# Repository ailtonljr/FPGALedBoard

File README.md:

# FPGALedBoard
Um módulo para a placa DE0-Nano com saídas em Leds e Display de 7 Segmentos.

Associação dos pinos da placa de saída com o FPGA:

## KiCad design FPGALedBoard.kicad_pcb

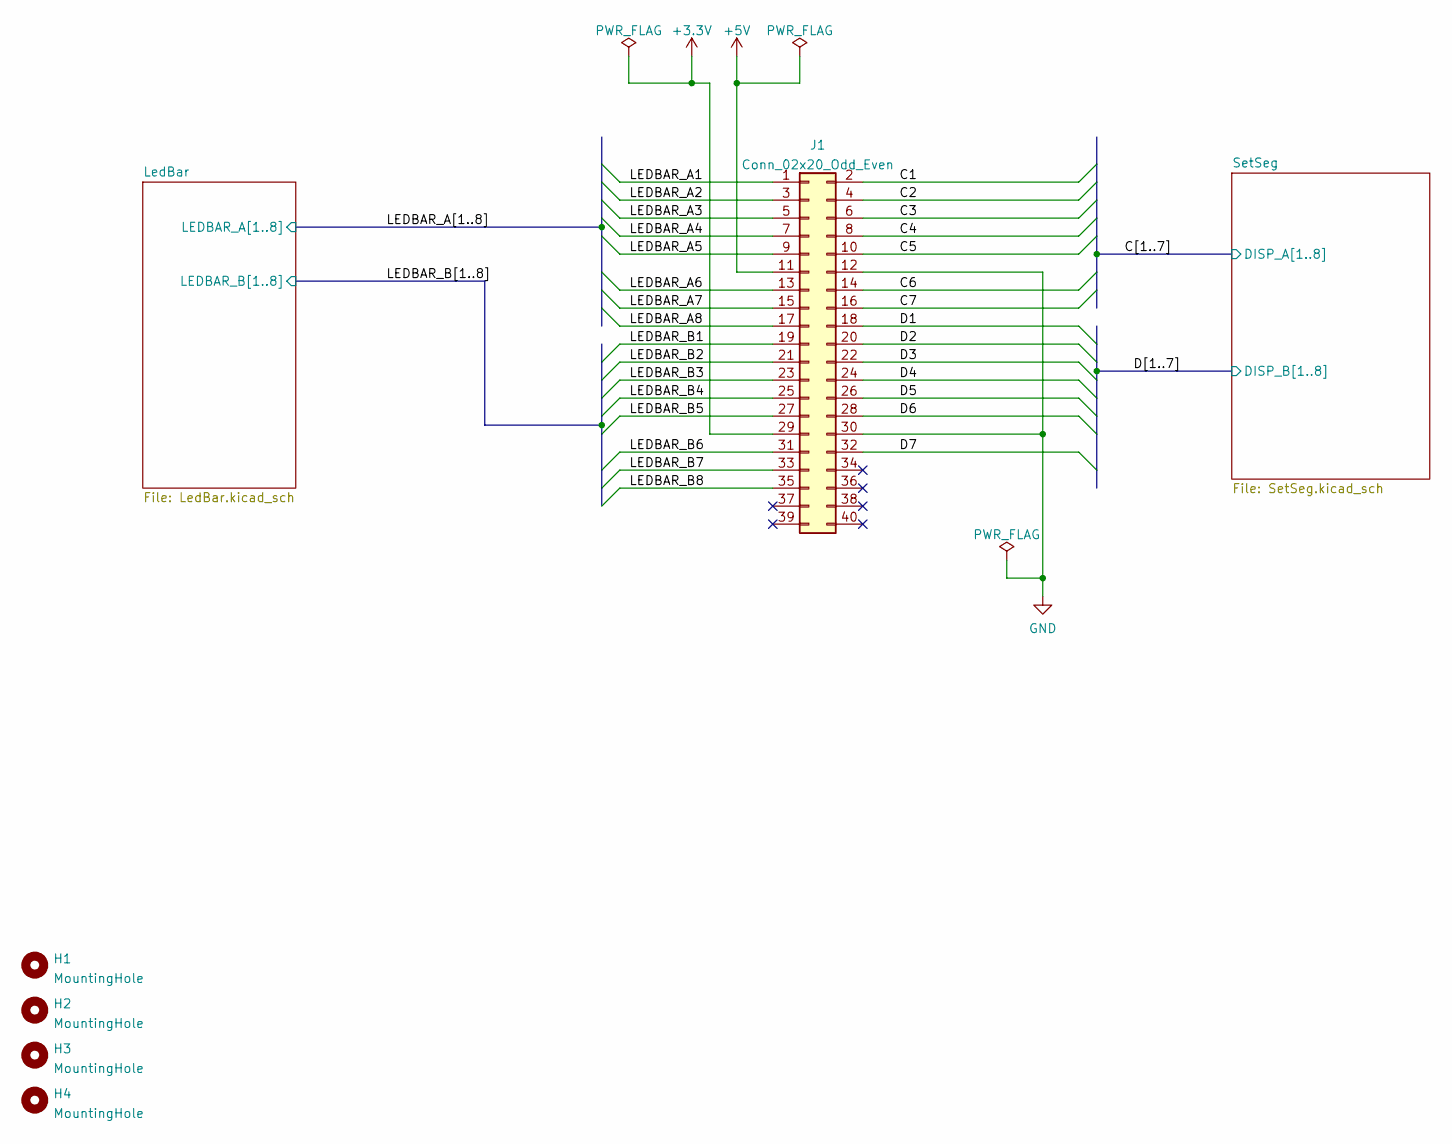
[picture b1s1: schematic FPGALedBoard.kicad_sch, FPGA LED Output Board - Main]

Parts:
H1, H2, H3, H4: MountingHole; MountingHole_3.2mm_M3
J1: Conn_02x20_Odd_Even; PinSocket_2x20_P2.54mm_Vertical

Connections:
+3V3: J1.29
+5V: J1.11; also elsewhere on the board
/C1: J1.2; also elsewhere on the board
/C2: J1.4; also elsewhere on the board
/C3: J1.6; also elsewhere on the board
/C4: J1.8; also elsewhere on the board
/C5: J1.10; also elsewhere on the board
/C6: J1.14; also elsewhere on the board
/C7: J1.16; also elsewhere on the board
/D1: J1.18; also elsewhere on the board
/D2: J1.20; also elsewhere on the board
/D3: J1.22; also elsewhere on the board
/D4: J1.24; also elsewhere on the board
/D5: J1.26; also elsewhere on the board
/D6: J1.28; also elsewhere on the board
/D7: J1.32; also elsewhere on the board
/LEDBAR_A1: J1.1; also elsewhere on the board
/LEDBAR_A2: J1.3; also elsewhere on the board
/LEDBAR_A3: J1.5; also elsewhere on the board
/LEDBAR_A4: J1.7; also elsewhere on the board
/LEDBAR_A5: J1.9; also elsewhere on the board
/LEDBAR_A6: J1.13; also elsewhere on the board
/LEDBAR_A7: J1.15; also elsewhere on the board
/LEDBAR_A8: J1.17; also elsewhere on the board
/LEDBAR_B1: J1.19; also elsewhere on the board
/LEDBAR_B2: J1.21; also elsewhere on the board
/LEDBAR_B3: J1.23; also elsewhere on the board
/LEDBAR_B4: J1.25; also elsewhere on the board
/LEDBAR_B5: J1.27; also elsewhere on the board
/LEDBAR_B6: J1.31; also elsewhere on the board
/LEDBAR_B7: J1.33; also elsewhere on the board
/LEDBAR_B8: J1.35; also elsewhere on the board
GND: J1.12, J1.30; also elsewhere on the board

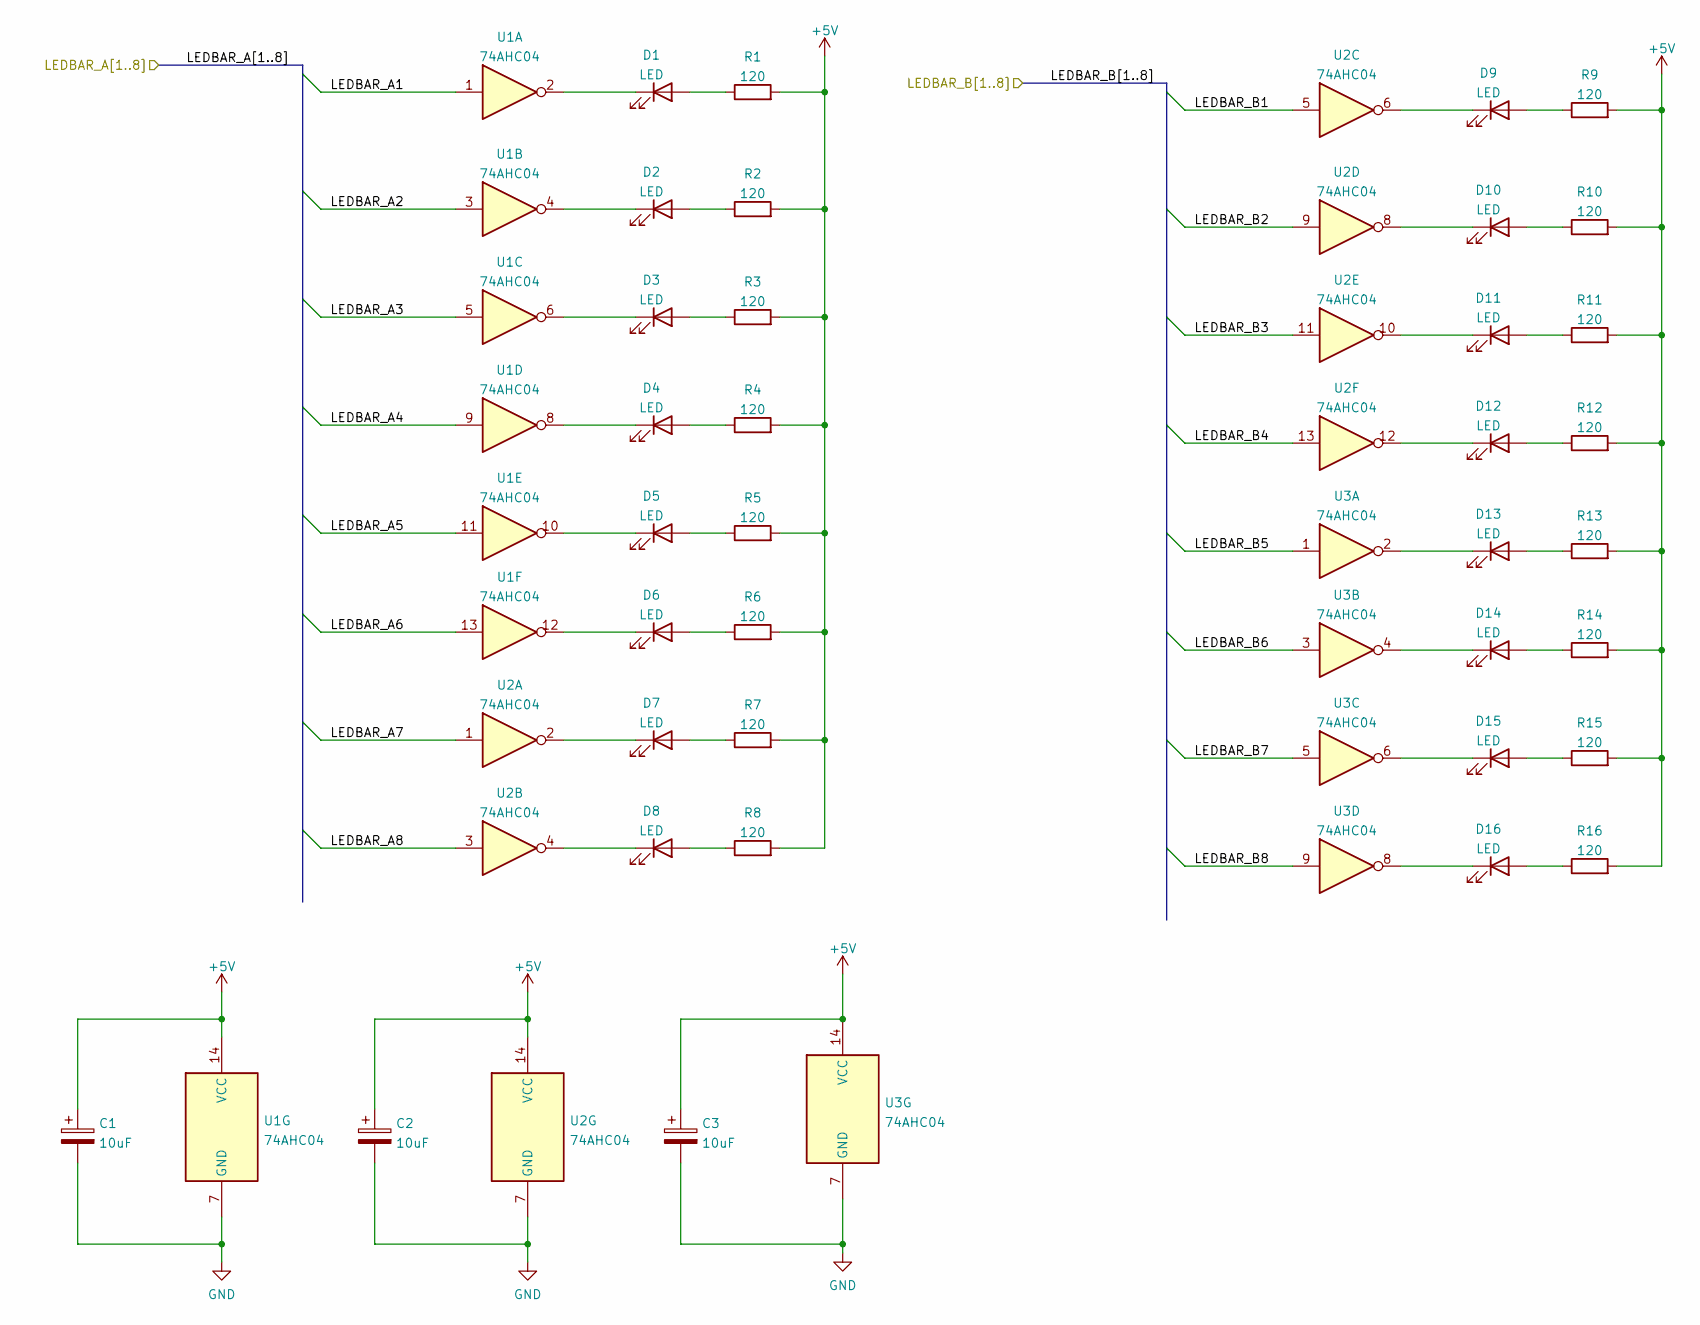
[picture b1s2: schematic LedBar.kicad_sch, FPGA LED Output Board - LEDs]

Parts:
C1, C2, C3: 10uF; CP_Radial_D5.0mm_P2.50mm
D1, D2, D3, D4, D5, D6, D7, D8, D9, D10, D11, D12, D13, D14, D15, D16: LED; LED_D3.0mm
R1, R2, R3, R4, R5, R6, R7, R8, R9, R10, R11, R12, R13, R14, R15, R16: 120; R_Axial_DIN0207_L6.3mm_D2.5mm_P7.62mm_Horizontal
U1, U2, U3: 74AHC04; DIP-14_W7.62mm

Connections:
+5V: C1.1, C2.1, C3.1, R1.2, R2.2, R3.2, R4.2, R5.2, R6.2, R7.2, R8.2, R9.2, R10.2, R11.2, R12.2, R13.2, R14.2, R15.2, R16.2, U1.14 (VCC), U2.14 (VCC), U3.14 (VCC); also elsewhere on the board
/LEDBAR_A1: U1.1; also elsewhere on the board
/LEDBAR_A2: U1.3; also elsewhere on the board
/LEDBAR_A3: U1.5; also elsewhere on the board
/LEDBAR_A4: U1.9; also elsewhere on the board
/LEDBAR_A5: U1.11; also elsewhere on the board
/LEDBAR_A6: U1.13; also elsewhere on the board
/LEDBAR_A7: U2.1; also elsewhere on the board
/LEDBAR_A8: U2.3; also elsewhere on the board
/LEDBAR_B1: U2.5; also elsewhere on the board
/LEDBAR_B2: U2.9; also elsewhere on the board
/LEDBAR_B3: U2.11; also elsewhere on the board
/LEDBAR_B4: U2.13; also elsewhere on the board
/LEDBAR_B5: U3.1; also elsewhere on the board
/LEDBAR_B6: U3.3; also elsewhere on the board
/LEDBAR_B7: U3.5; also elsewhere on the board
/LEDBAR_B8: U3.9; also elsewhere on the board
GND: C1.2, C2.2, C3.2, U1.7 (GND), U2.7 (GND), U3.7 (GND); also elsewhere on the board
unnamed: D1.1 (K), U1.2
unnamed: D1.2 (A), R1.1
unnamed: D2.1 (K), U1.4
unnamed: D2.2 (A), R2.1
unnamed: D3.1 (K), U1.6
unnamed: D3.2 (A), R3.1
unnamed: D4.1 (K), U1.8
unnamed: D4.2 (A), R4.1
unnamed: D5.1 (K), U1.10
unnamed: D5.2 (A), R5.1
unnamed: D6.1 (K), U1.12
unnamed: D6.2 (A), R6.1
unnamed: D7.1 (K), U2.2
unnamed: D7.2 (A), R7.1
unnamed: D8.1 (K), U2.4
unnamed: D8.2 (A), R8.1
unnamed: D9.1 (K), U2.6
unnamed: D9.2 (A), R9.1
unnamed: D10.1 (K), U2.8
unnamed: D10.2 (A), R10.1
unnamed: D11.1 (K), U2.10
unnamed: D11.2 (A), R11.1
unnamed: D12.1 (K), U2.12
unnamed: D12.2 (A), R12.1
unnamed: D13.1 (K), U3.2
unnamed: D13.2 (A), R13.1
unnamed: D14.1 (K), U3.4
unnamed: D14.2 (A), R14.1
unnamed: D15.1 (K), U3.6
unnamed: D15.2 (A), R15.1
unnamed: D16.1 (K), U3.8
unnamed: D16.2 (A), R16.1

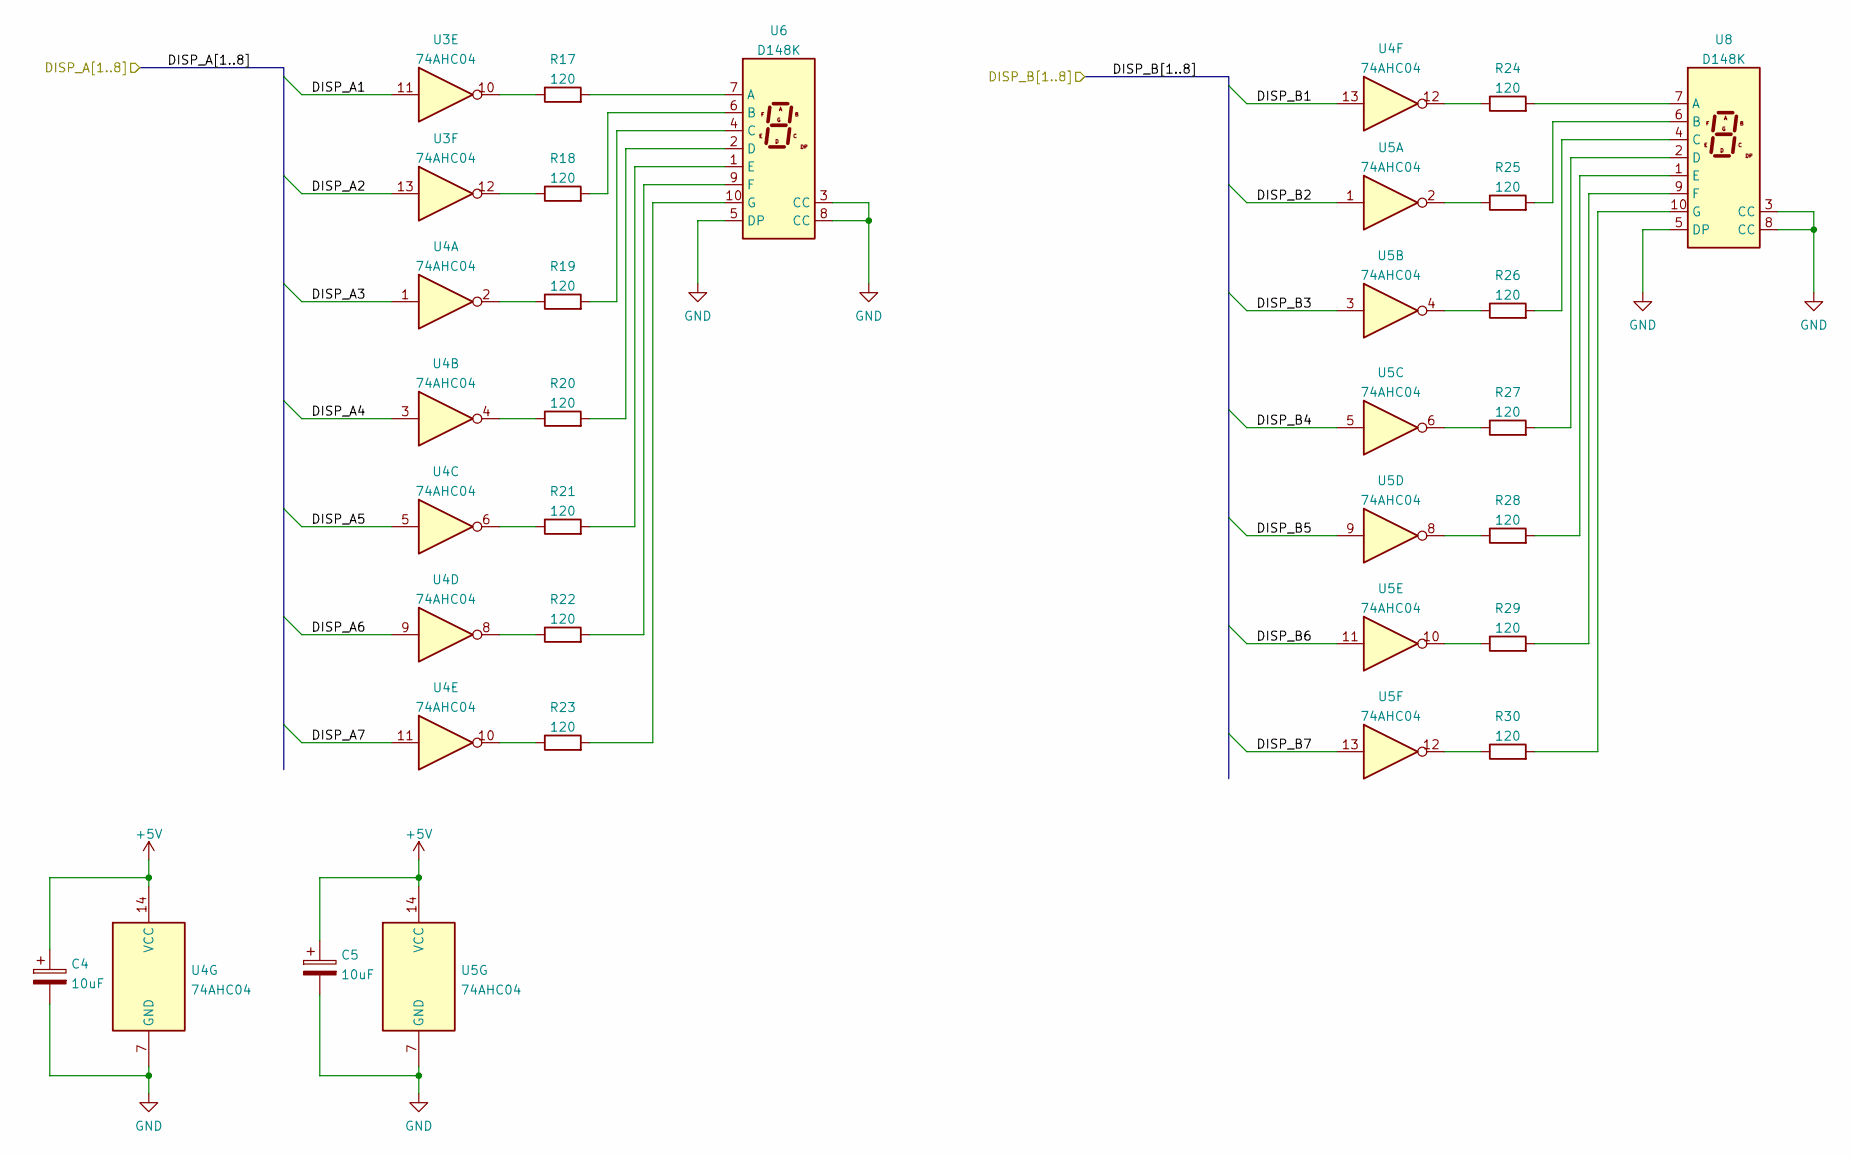
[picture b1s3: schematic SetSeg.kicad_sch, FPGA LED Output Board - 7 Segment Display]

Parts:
C4, C5: 10uF; CP_Radial_D5.0mm_P2.50mm
R17, R18, R19, R20, R21, R22, R23, R24, R25, R26, R27, R28, R29, R30: 120; R_Axial_DIN0207_L6.3mm_D2.5mm_P7.62mm_Horizontal
U3, U4, U5: 74AHC04; DIP-14_W7.62mm
U6, U8: D148K; D1X8K

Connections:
+5V: C4.1, C5.1, U4.14 (VCC), U5.14 (VCC); also elsewhere on the board
/C1: U3.11; also elsewhere on the board
/C2: U3.13; also elsewhere on the board
/C3: U4.1; also elsewhere on the board
/C4: U4.3; also elsewhere on the board
/C5: U4.5; also elsewhere on the board
/C6: U4.9; also elsewhere on the board
/C7: U4.11; also elsewhere on the board
/D1: U4.13; also elsewhere on the board
/D2: U5.1; also elsewhere on the board
/D3: U5.3; also elsewhere on the board
/D4: U5.5; also elsewhere on the board
/D5: U5.9; also elsewhere on the board
/D6: U5.11; also elsewhere on the board
/D7: U5.13; also elsewhere on the board
GND: C4.2, C5.2, U4.7 (GND), U5.7 (GND), U6.3 (CC), U6.5 (DP), U6.8 (CC), U8.3 (CC), U8.5 (DP), U8.8 (CC); also elsewhere on the board
unnamed: R17.1, U3.10
unnamed: R17.2, U6.7 (A)
unnamed: R18.1, U3.12
unnamed: R18.2, U6.6 (B)
unnamed: R19.1, U4.2
unnamed: R19.2, U6.4 (C)
unnamed: R20.1, U4.4
unnamed: R20.2, U6.2 (D)
unnamed: R21.1, U4.6
unnamed: R21.2, U6.1 (E)
unnamed: R22.1, U4.8
unnamed: R22.2, U6.9 (F)
unnamed: R23.1, U4.10
unnamed: R23.2, U6.10 (G)
unnamed: R24.1, U4.12
unnamed: R24.2, U8.7 (A)
unnamed: R25.1, U5.2
unnamed: R25.2, U8.6 (B)
unnamed: R26.1, U5.4
unnamed: R26.2, U8.4 (C)
unnamed: R27.1, U5.6
unnamed: R27.2, U8.2 (D)
unnamed: R28.1, U5.8
unnamed: R28.2, U8.1 (E)
unnamed: R29.1, U5.10
unnamed: R29.2, U8.9 (F)
unnamed: R30.1, U5.12
unnamed: R30.2, U8.10 (G)

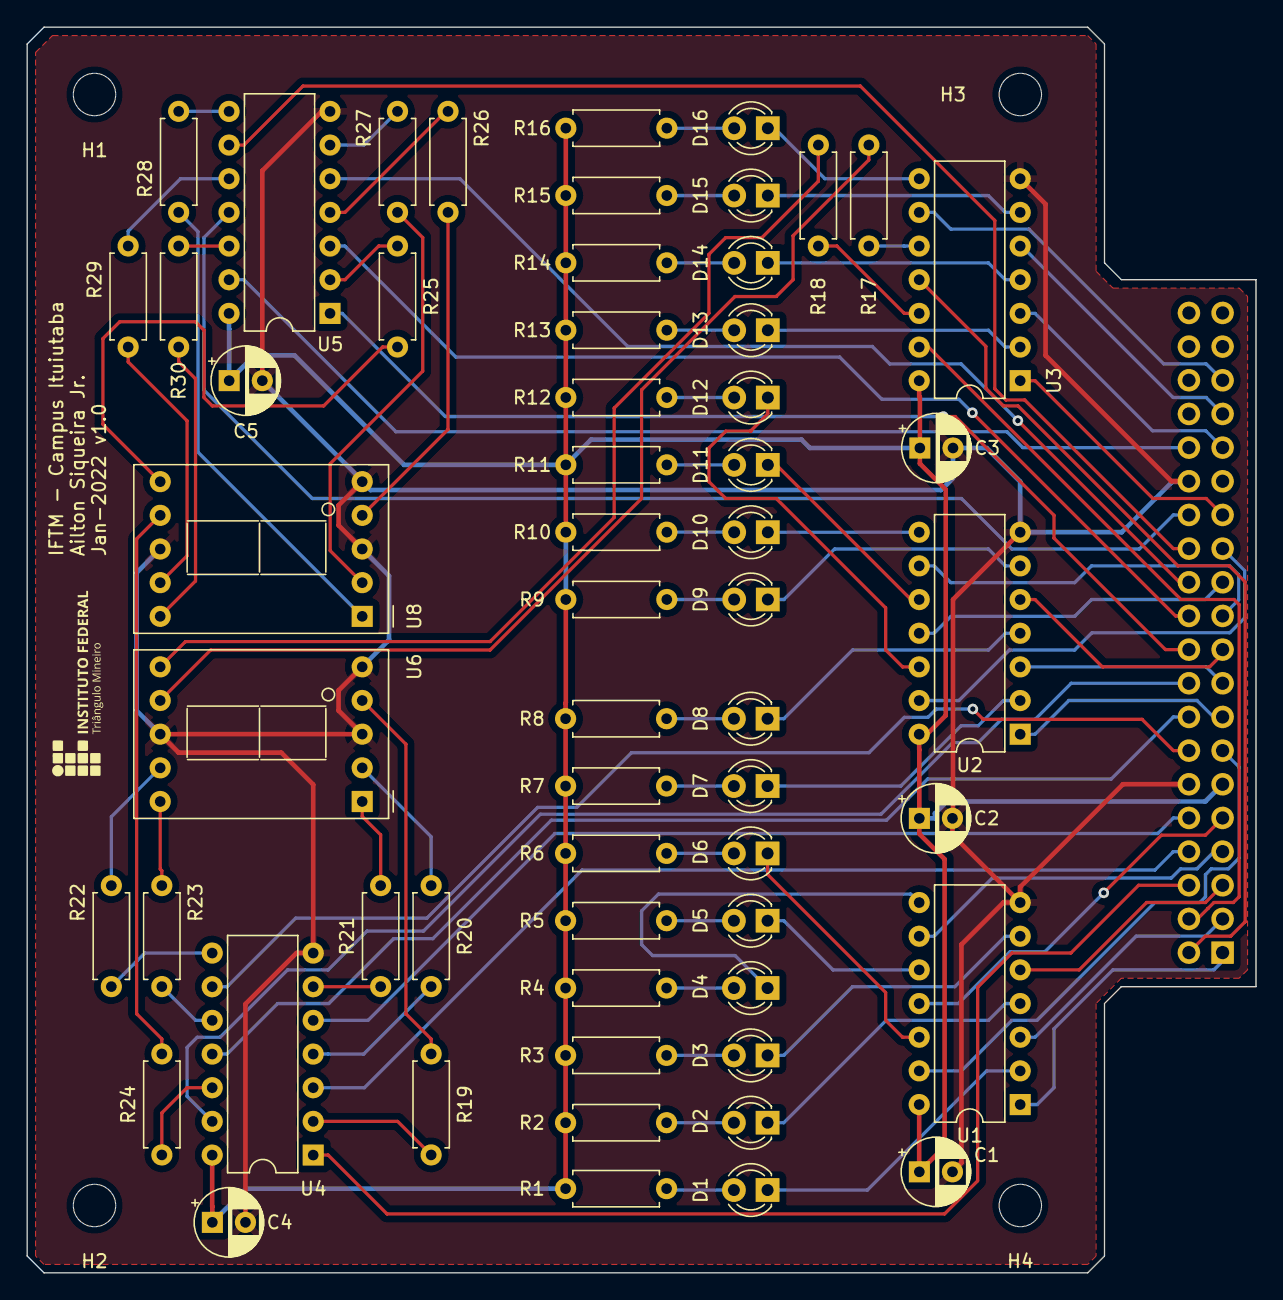
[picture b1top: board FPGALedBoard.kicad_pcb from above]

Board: 2 copper layers, 92.7 x 94.0 mm, 63 parts (1 on the bottom side), 92 nets.

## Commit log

2022-01-21 Primeiro commit
2022-01-25 Atualizados os Footprints. Definido um primeiro corte da placa.
2022-01-26 Placa roeada automaticamente.
2022-01-31 Pequenas melhorias no Layout da placa
2022-02-01 Corrigido um erro na linha de 3.3V. Adicionado o Ground Plane.
2022-11-01 Add files via upload
    Adicionado uma figura com o esquema de ligação do FPGA com a placa.
